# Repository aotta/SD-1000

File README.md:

# SD-1000
Sega flash multicart for SC-3000, SG-1000 and Mark III based on Pico Clone

SD-1000 is a multicart DIY yourself based on cheap "purple" Raspberry Pi Pico clone.

**WARNING!** "purple" Pico has not the same pinout of original Raspberry "green" ones, you MUST use the clone or you may damage your hardware.

Kicad project and gerbers files for the pcb are in the PCB folder, you need only a diode and a push buttons. The jumper for 5V to B3 must left open.
Add you pico clone, and flash the firmware SD1000_cart.uf2 in the Pico by connecting it while pressing button on Pico and drop it in the opened windows on PC.
After flashed with firmware, and every time you have to change your ROMS repository, you can simpli connect the Pico to PC and drag&drop "BIN","ROM","SG","SC" or "SMS" files into.

Even if the diode should protect your console, **DO NOT CONNECT PICO WHILE INSERTED IN A POWERED ON CONSOLE!**

## NOTE:
I added v. 1.01 which fixes Ninja Princess and Golgo for SC-3000, and last v.1.02 that works with SG-1000 and Mark III. If you have only the SC-3000, i suggest you use the 1.01 FW

18/09/26 I moved to Arduino IDE, and made v.1.03 that should be more compatible with games but Mark III no more supported. WARNING: if you flash this version from a previous one, you must RE-FORMAT flash and re-upload games

## Credits
I have to thanks some friends for helping me in completing this projects in few time:

Thank to Robin Robin Edwards and his A8PicoCart (https://github.com/robinhedwards/A8PicoCart), i found very smart his way to manage the Flash RAM and the USB updates, so i admit i took large parte of his code for it!.

I used also the new and fantastic CVBasic for writing menu and file selector in Sega, thank to Oscar Toledo (https://nanochess.org/) for creating it and supporting me in an issue with SC-3000.

And, last but not least, a special thank to my friend Fabio (https://github.com/fabiodl) that from Japan leaded me out of a couple of tricky steps.

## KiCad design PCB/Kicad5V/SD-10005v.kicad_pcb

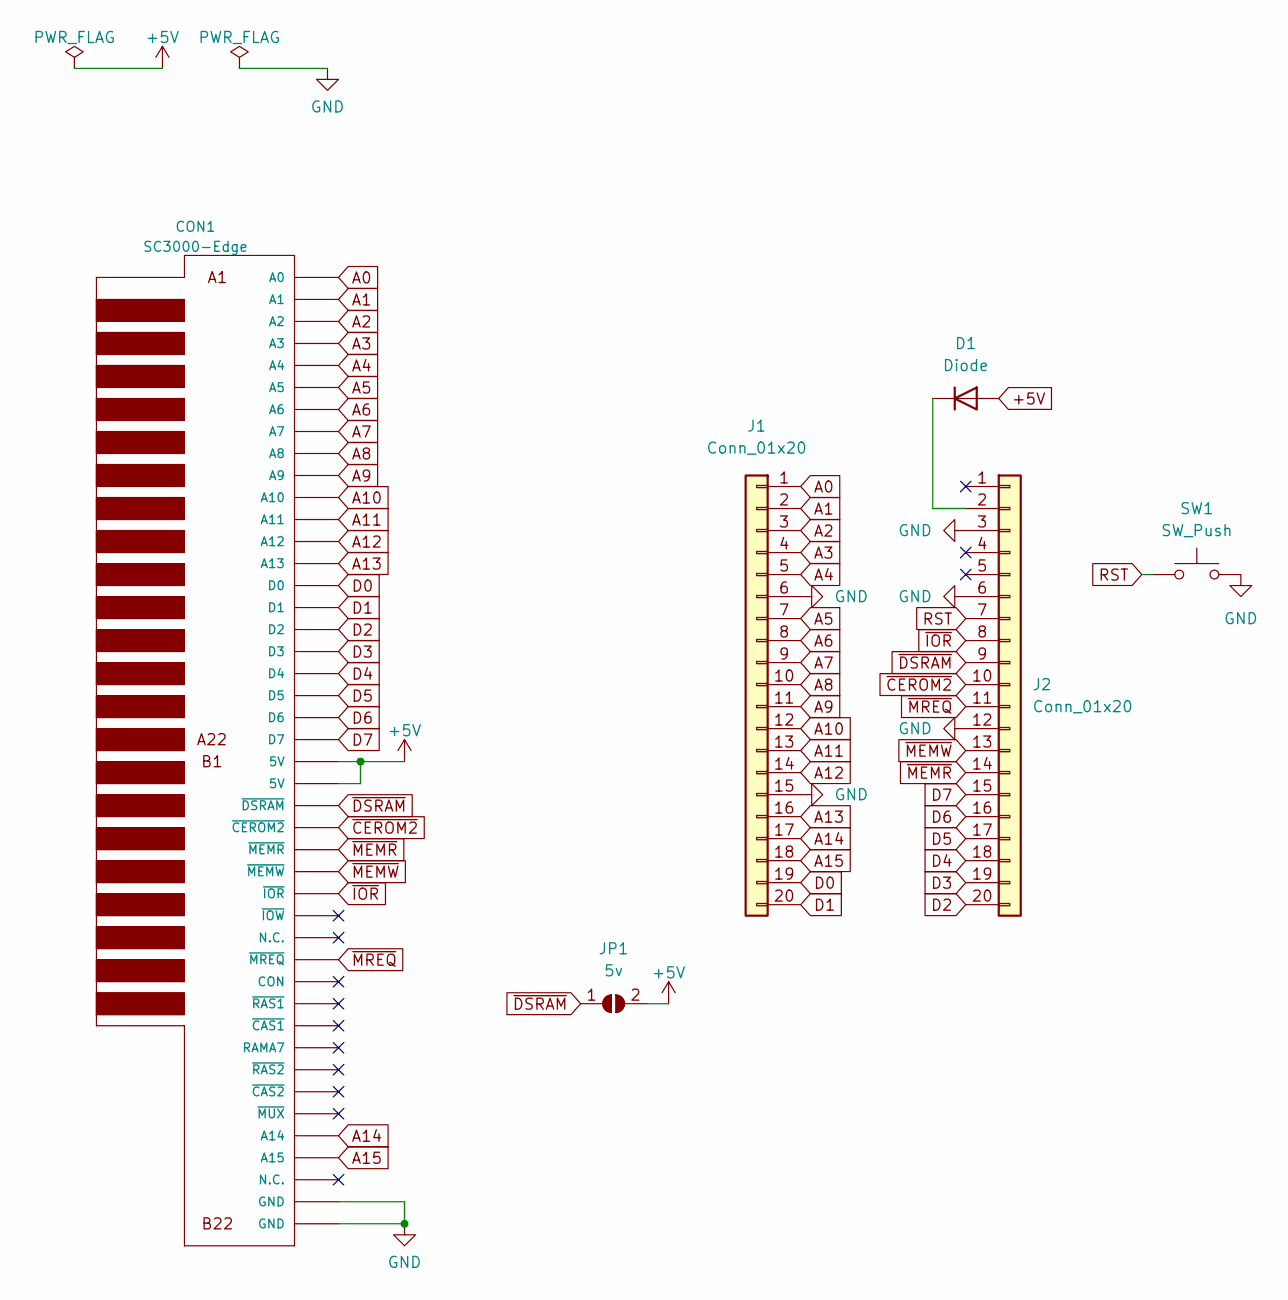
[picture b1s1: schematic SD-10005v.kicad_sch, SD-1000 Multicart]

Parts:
CON1: SC3000-Edge; CartridgeEdge
D1: Diode; D_DO-35_SOD27_P7.62mm_Horizontal
J1, J2: Conn_01x20; PinSocket_1x20_P2.54mm_Vertical
JP1: 5v; SolderJumper-2_P1.3mm_Open_Pad1.0x1.5mm
SW1: SW_Push; SW_PUSH_6mm

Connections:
+5V: CON1.B1 (5V), CON1.B2 (5V), D1.2 (A), JP1.2 (B)
A0: CON1.A1 (A0), J1.1
A1: CON1.A2 (A1), J1.2
A2: CON1.A3 (A2), J1.3
A3: CON1.A4 (A3), J1.4
A4: CON1.A5 (A4), J1.5
A5: CON1.A6 (A5), J1.7
A6: CON1.A7 (A6), J1.8
A7: CON1.A8 (A7), J1.9
A8: CON1.A9 (A8), J1.10
A9: CON1.A10 (A9), J1.11
A10: CON1.A11 (A10), J1.12
A11: CON1.A12 (A11), J1.13
A12: CON1.A13 (A12), J1.14
A13: CON1.A14 (A13), J1.16
A14: CON1.B18 (A14), J1.17
A15: CON1.B19 (A15), J1.18
D0: CON1.A15 (D0), J1.19
D1: CON1.A16 (D1), J1.20
D2: CON1.A17 (D2), J2.20
D3: CON1.A18 (D3), J2.19
D4: CON1.A19 (D4), J2.18
D5: CON1.A20 (D5), J2.17
D6: CON1.A21 (D6), J2.16
D7: CON1.A22 (D7), J2.15
GND: CON1.B21 (GND), CON1.B22 (GND), J1.6, J1.15, J2.3, J2.6, J2.12, SW1.2
unnamed: D1.1 (K), J2.2
RST: J2.7, SW1.1
~CEROM2: CON1.B4 (~CEROM2), J2.10
~DSRAM: CON1.B3 (~DSRAM), J2.9, JP1.1 (A)
~IOR: CON1.B7 (~IOR), J2.8
~MEMR: CON1.B5 (~MEMR), J2.14
~MEMW: CON1.B6 (~MEMW), J2.13
~MREQ: CON1.B10 (~MREQ), J2.11

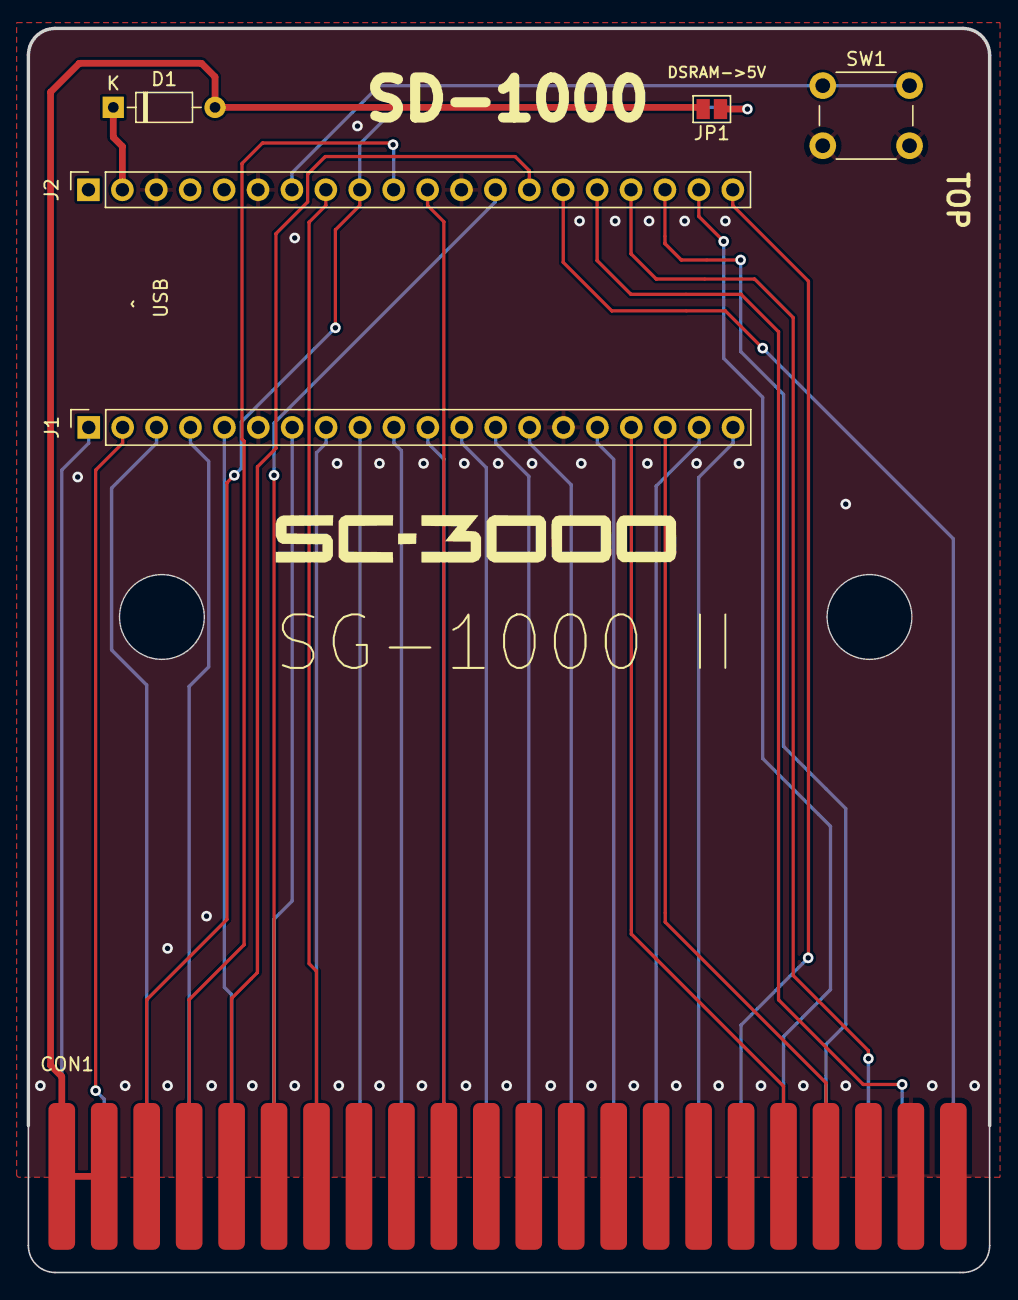
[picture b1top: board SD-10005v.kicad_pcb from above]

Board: 2 copper layers, 72.0 x 93.1 mm, 6 parts (0 on the bottom side), 34 nets.

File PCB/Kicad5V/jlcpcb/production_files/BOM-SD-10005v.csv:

Designator,Footprint,Quantity,Value,LCSC Part #
CON1,CartridgeEdge,1,SC3000-Edge,
D1,D_DO-35_SOD27_P7.62mm_Horizontal,1,Diode,
"J1, J2",PinSocket_1x20_P2.54mm_Vertical,2,Conn_01x20,
JP1,SolderJumper-2_P1.3mm_Open_Pad1.0x1.5mm,1,5v,
SW1,SW_PUSH_6mm,1,SW_Push,

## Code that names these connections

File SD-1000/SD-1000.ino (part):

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#define D5_PIN   21
#define D6_PIN   22
#define D7_PIN   23
#define MEMR_PIN  24
#define MEMW_PIN  25
#define MREQ_PIN  26
#define CEROM2_PIN  27
#define DSRAM_PIN  28 
#define IOR_PIN  29 

// Pico pin usage masks

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    
  while (1)
 {
    while ((pins = gpio_get_all()) & MREQ_PIN_MASK ); //removed for compatibility with SG-1000, which doesn't have IOR
   
    pins = gpio_get_all();   // to keep for SG-1000 compatibility, we read the pins again after the wait for MREQ to go low
	
    addr = pins & BUS_PIN_MASK;

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  //
   
  gpio_init_mask(ALL_GPIO_MASK);
  pinMode(DSRAM_PIN,OUTPUT);
  digitalWrite(DSRAM_PIN,HIGH);

 // Initialize the bus state variables
  
  
  pinMode(CEROM2_PIN,INPUT);
 
 bool carton = false;
  int t = 100;
  
  while (gpio_get(CEROM2_PIN) == 0 && to_ms_since_boot(get_absolute_time()) < 2000) {
    if (to_ms_since_boot(get_absolute_time()) > t) {
      t += 100;
    }
    sleep_ms(1);
  }
  
 if (gpio_get(CEROM2_PIN) == 1) {
    carton = true;  
 }
  
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
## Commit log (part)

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2024-04-25 Add files via upload
    Initial realease
2024-04-25 Add files via upload
    added pictures
2024-04-25 Update README.md
    writing...
2024-04-25 Update README.md
    editing
2024-04-26 Add files via upload
    bug fixed in CVBasic, changed rom.h and recompiled firmware
2024-04-26 Add files via upload
    bug fixed in cvbasic, rom.h and cvs_basic_prologue.asm updated
2024-04-26 Add files via upload
    bug fixed in cvbasic, rom.h and cvs_basic_prologue.asm updated. Use this patched version (ram and stack map are different) when compiling for SD-1000
2024-04-27 Update README.md
    3d cover added
2024-04-27 Add files via upload
    lowered usb hole
2024-04-27 Add files via upload
    added shell picture
2024-05-11 Add files via upload
    added Sc-3000 keyboard support, thank to https://github.com/siriokds/SC-3000-Keyboard-support/
2024-05-11 Add files via upload
    Addedd SC-3000 keyboard support in menu, thanks to https://github.com/siriokds/SC-3000-Keyboard-support/
2024-05-11 Add files via upload
    version with SC-3000 keyboard support, thank to SirioKid
2024-06-03 Add files via upload
    bug fixed for game greater than 40k
2024-06-03 Add files via upload
    bug fixed for roms greater than 40k
2024-10-04 Update PCB
    -- Ground plane added to TOP & BOTTOM layer
    -- Better routing for some tracks
    -- Production files updated
    -- JLCPCB DRU file added
2025-08-10 Re-positioning PCB
    Slided of 3mm PCB for better compatibility with SG-1000
